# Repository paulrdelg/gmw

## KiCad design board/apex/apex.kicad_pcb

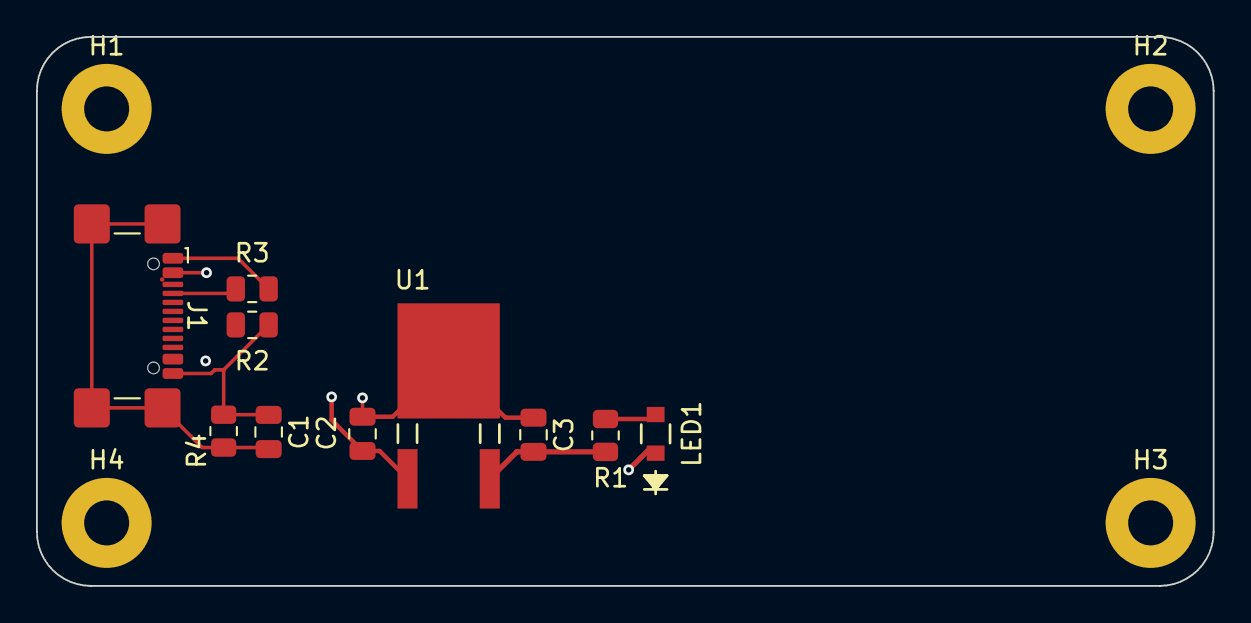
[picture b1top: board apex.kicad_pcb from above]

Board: 4 copper layers, 65.4 x 30.5 mm, 14 parts (0 on the bottom side), 7 nets.

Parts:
C1: 0.1 uF; C_0805_2012Metric
C2, C3: 10 uF; C_0805_2012Metric
H1: H1_MH; MountingHole_2.5mm_Pad
H2: H2_MH; MountingHole_2.5mm_Pad
H3: H3_MH; MountingHole_2.5mm_Pad
H4: H4_MH; MountingHole_2.5mm_Pad
J1: USB_C_Receptacle_USB2.0_16P; USB_C_Receptacle_GCT_USB4110
LED1: 150080BS75000; LED_BS75000_WRE
R1: 3.3; R_0805_2012Metric
R2, R3: 5.1k; R_0805_2012Metric
R4: 330; R_0805_2012Metric
U1: AP7363-33D-13; TO252-3L_DIO

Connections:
+3V3: C3.2, R1.2, U1.3 (OUT)
GND: C1.1, C2.1, C3.1, J1.A1 (GND), J1.A12 (GND), J1.B1 (GND), J1.B12 (GND), LED1.1, R2.2, R3.2, R4.1, U1.2 (GND)
GNDPWR: C1.2, J1.S1 (SHIELD), R4.2
unnamed: J1.A5 (CC1), R3.1
unnamed: J1.B5 (CC2), R2.1
unnamed: LED1.2, R1.1
VBUS: C2.2, J1.A4 (VBUS), J1.A9 (VBUS), J1.B4 (VBUS), J1.B9 (VBUS), U1.1 (IN)

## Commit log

2023-04-23 creation entry file
2024-03-24 added gitignore
2024-03-24 update compile to 08
2024-03-31 added spec
2024-04-26 created board project
2024-04-30 added usb to board schematic
2024-05-01 testing adding usb 3D model
2024-05-02 added power input/outputs
2024-05-05 added SMDs to board
2024-05-11 started routing
2024-05-11 added models
2024-05-16 deleted zip
2024-05-17 organized modules
2024-05-17 updated schematic
2024-05-18 checked parity with schematic
2024-05-19 expanded LED pads
2024-05-20 added 3d models; added TVS diodes
2024-05-20 added dark theme
